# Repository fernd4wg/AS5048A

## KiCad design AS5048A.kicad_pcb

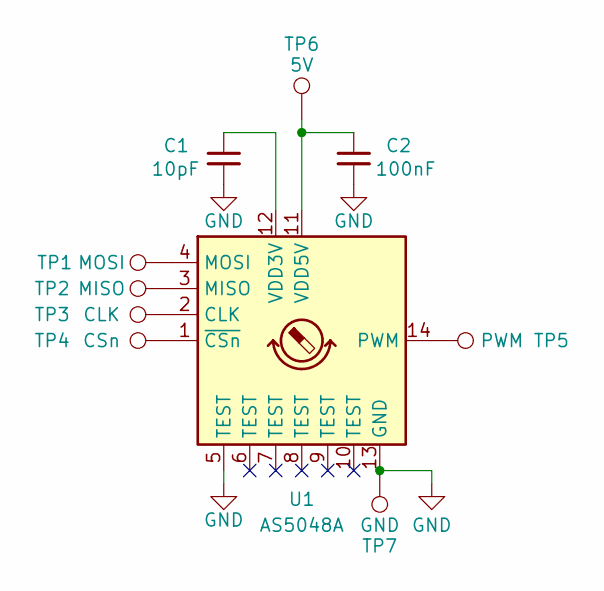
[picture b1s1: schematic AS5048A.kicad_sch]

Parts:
C1: 10pF; C_0201_0603Metric
C2: 100nF; C_0201_0603Metric
TP1: MOSI; TestPoint_Pad_1.5x1.5mm
TP2: MISO; TestPoint_Pad_1.5x1.5mm
TP3: CLK; TestPoint_Pad_1.5x1.5mm
TP4: CSn; TestPoint_Pad_1.5x1.5mm
TP5: PWM; TestPoint_Pad_1.5x1.5mm
TP6: 5V; TestPoint_Pad_1.5x1.5mm
TP7: GND; TestPoint_Pad_1.5x1.5mm
U1: AS5048A; TSSOP-14_4.4x5mm_P0.65mm

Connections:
GND: C1.2, C2.2, TP7.1 (1_1), U1.5 (TEST), U1.13 (GND)
unnamed: TP3.1 (1_1), U1.2 (CLK)
unnamed: TP2.1 (1_1), U1.3 (MISO)
unnamed: TP1.1 (1_1), U1.4 (MOSI)
unnamed: TP5.1 (1_1), U1.14 (PWM)
unnamed: C1.1, U1.12 (VDD3V)
unnamed: C2.1, TP6.1 (1_1), U1.11 (VDD5V)
unnamed: TP4.1 (1_1), U1.1 (~CSn)

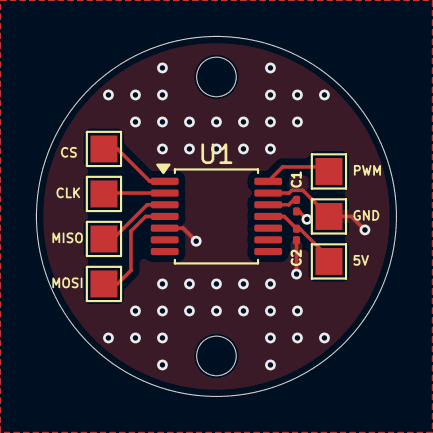
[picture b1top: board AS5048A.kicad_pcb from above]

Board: 2 copper layers, 20.0 x 20.0 mm, 10 parts (0 on the bottom side), 8 nets.
